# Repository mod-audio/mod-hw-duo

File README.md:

mod-hw-duo
=======================

This repository contains the schematics and PCB design files for the MOD Duo hardware (http://moddevices.com/).

These files were created and can be improved with KiCAD, a free software Electronics CAD which is available at http://www.kicad.org/

This project should work with last revision of KiCad libraries and footprints available at https://github.com/KiCad/

## License

Copyright (c) 2014-2026 MOD Audio Limited.

The hardware design files (schematics, PCB layouts, fabrication files, BOMs) are licensed under
[CC BY-NC-SA 4.0](https://creativecommons.org/licenses/by-nc-sa/4.0/) (see [`LICENSE`](LICENSE)).
You may study, modify, repair and build them for yourself, and share your changes under the same licence.
You may not use them commercially, for example to make or sell boards or devices.

Third-party files (manufacturer component models, symbols and footprints, module documentation) are not covered by
this licence. See [`NOTICE`](NOTICE) for the list.

The MOD logo is a registered trademark (EU trade mark no. 016228827; UK trade mark no. UK00916228827).
The licence gives no right to use the MOD name or logo. See [`NOTICE`](NOTICE).

For commercial licensing, contact MOD Audio.

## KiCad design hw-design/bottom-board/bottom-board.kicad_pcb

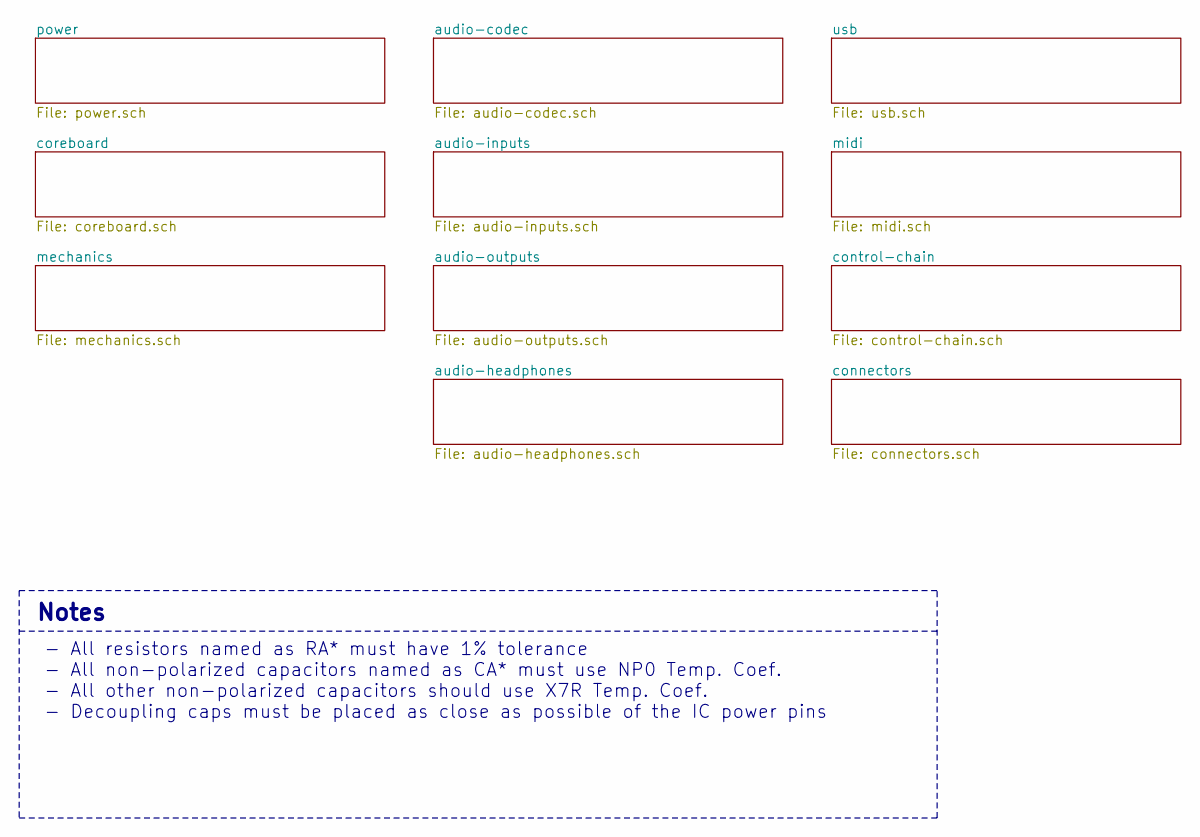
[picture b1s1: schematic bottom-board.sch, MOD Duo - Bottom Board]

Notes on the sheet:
- All resistors named as RA* must have 1% tolerance - All non-polarized capacitors named as CA* must use NP0 Temp. Coef. - All other non-polarized capacitors should use X7R Temp. Coef. - Decoupling caps must be placed as close as possible of the IC power pins
Notes

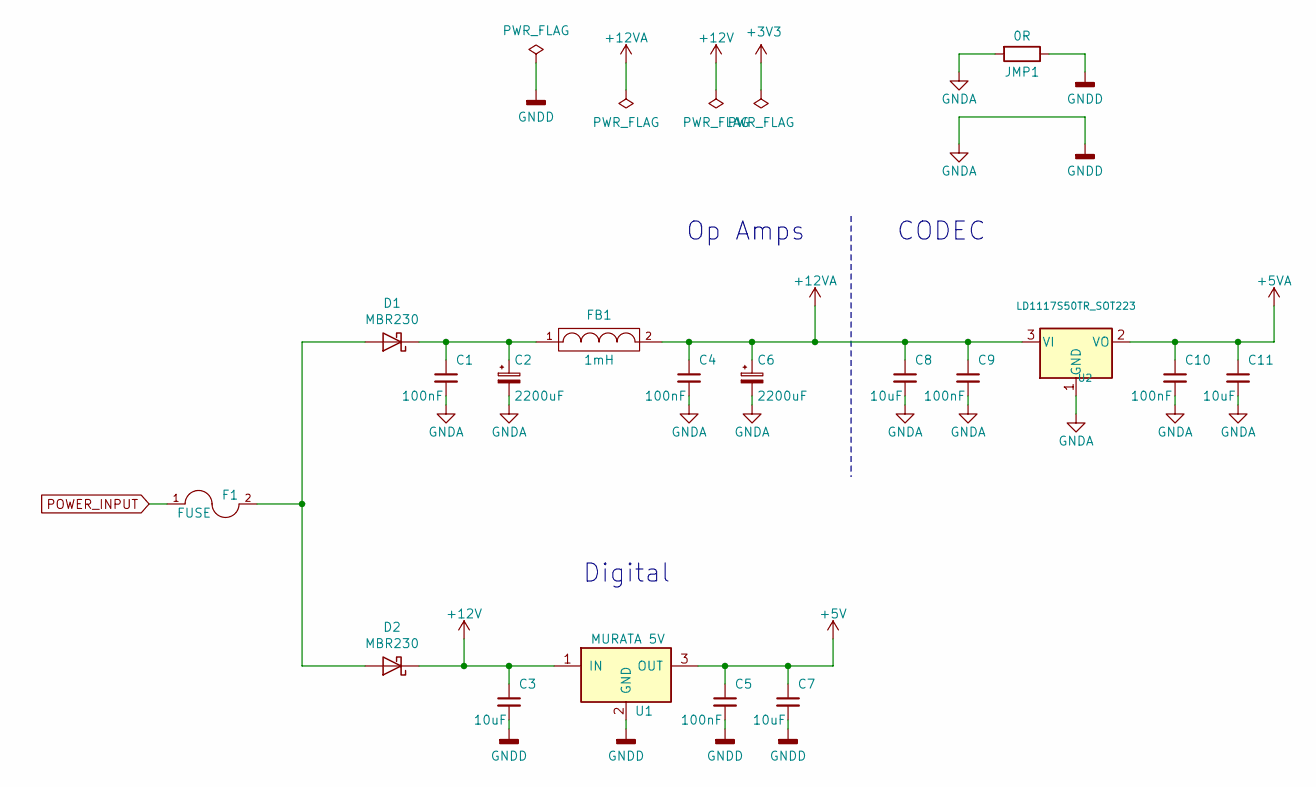
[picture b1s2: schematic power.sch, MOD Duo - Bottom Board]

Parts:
C1, C4, C5, C9, C10: 100nF; C_0603_1608Metric; MPN C1608X7R1E104K080AA
C2, C6: 2200uF; C_Radial_D10_L20_P5; MPN 16PX2200MEFC10X20
C3, C7, C8, C11: 10uF; C_0805_2012Metric; MPN GRM219R61E106KA12D
D1, D2: MBR230; D_SOD-123F
F1: FUSE; Fuse_SMD2920; MPN 0ZCF0200FF2C
FB1: 1mH; SELF-WE-PD-XXL; MPN SRR1260-102K
JMP1: 0R; Jumper_SMD_THT
U1: MURATA 5V; OKI-78SR_Vertical; MPN OKI-78SR-5/1.5-W36-C
U2: LD1117S50TR_SOT223; SOT-223-3_TabPin2; MPN NCP1117DT50G

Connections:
+5V: C5.1, C7.1, U1.3 (OUT); also elsewhere on the board
+5VA: C10.1, C11.1, U2.2 (VO); also elsewhere on the board
+12V: C3.1, D2.1 (K), U1.1 (IN); also elsewhere on the board
+12VA: C4.1, C6.1, C8.1, C9.1, FB1.2, U2.3 (VI); also elsewhere on the board
GNDA: C1.2, C2.2, C3.2, C4.2, C5.2, C6.2, C7.2, C8.2, C9.2, C10.2, C11.2, JMP1.1, JMP1.2, U1.2 (GND), U2.1 (GND); also elsewhere on the board
unnamed: C1.1, C2.1, D1.1 (K), FB1.1
unnamed: D1.2 (A), D2.2 (A), F1.2
POWER_INPUT: F1.1; also elsewhere on the board

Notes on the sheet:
Op Amps
CODEC
Digital

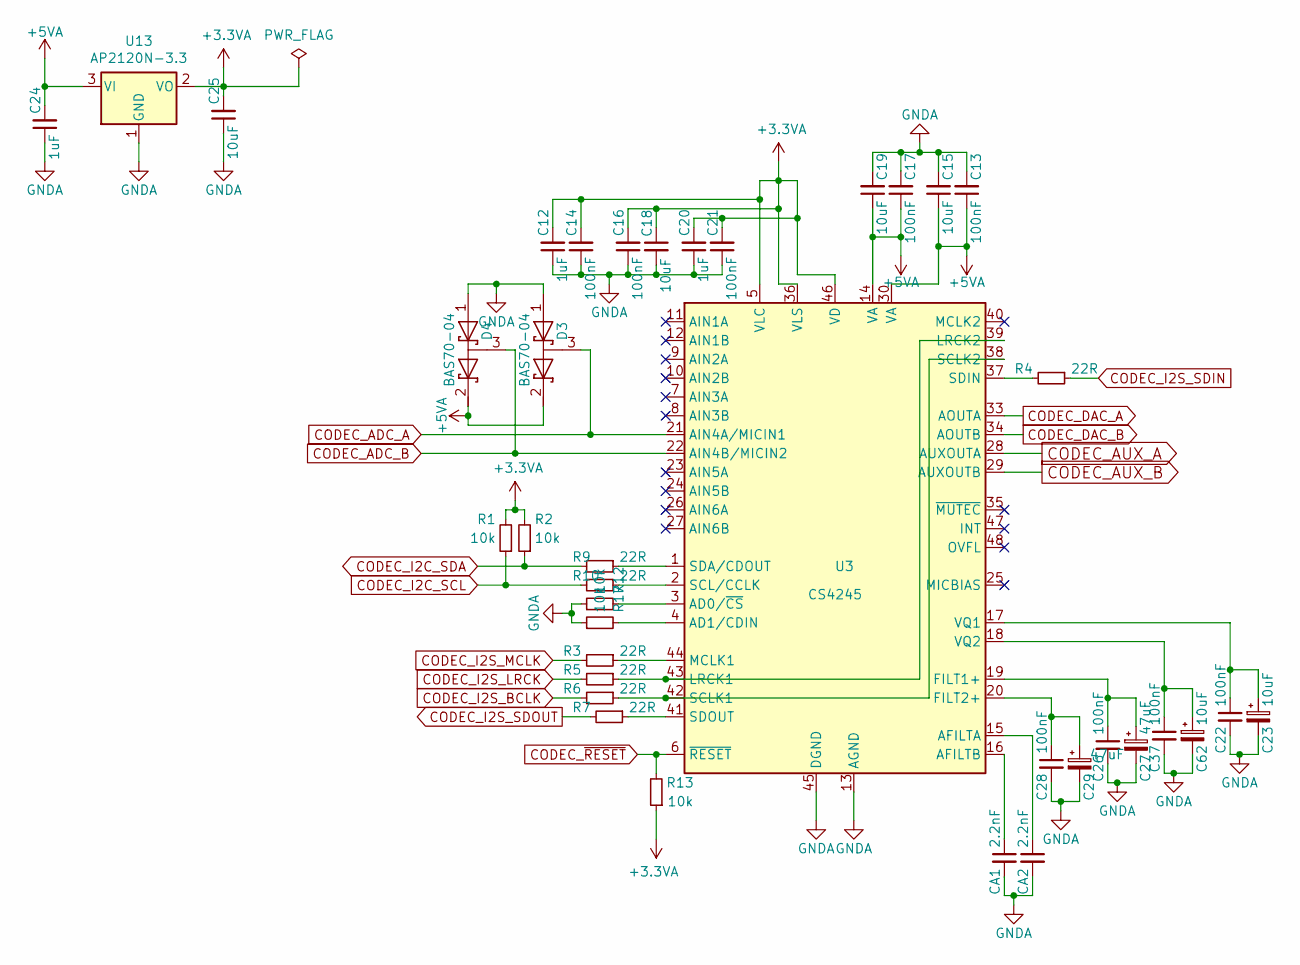
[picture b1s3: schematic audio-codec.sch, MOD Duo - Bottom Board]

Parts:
C12, C20, C24: 1uF; C_0805_2012Metric; MPN C2012X7R1E105K125AB
C13, C14, C16, C17, C21, C22, C26, C28, C37: 100nF; C_0402_1005Metric; MPN C1005X7R1E104K050BB
C15, C18, C19, C25: 10uF; C_0805_2012Metric; MPN GRM219R61E106KA12D
C23, C62: 10uF; CP_Elec_6.3x5.3; MPN UWX1E100MCL1GB
C27, C29: 47uF; CP_Elec_6.3x5.3; MPN UUD1E470MCL1GS
CA1, CA2: 2.2nF; C_0603_1608Metric; MPN GRM1885C1H222JA01D
D3, D4: BAS70-04; SOT-23; MPN BAS70-04-TP
R1, R2, R12, R13, R17: 10k; R_0603_1608Metric; MPN RMCF0603JT10K0
R3, R4, R5, R6, R7, R9, R10: 22R; R_0603_1608Metric; MPN RMCF0603JT22R0
U3: CS4245; LQFP-48_7x7mm_P0.5mm
U13: AP2120N-3.3; SOT-23

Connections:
+3.3VA: C12.2, C14.2, C16.2, C18.1, C20.2, C21.2, C25.2, R1.2, R2.2, R13.1, U3.5 (VLC), U3.36 (VLS), U3.46 (VD), U13.2 (VO)
+5VA: C13.1, C15.1, C17.1, C19.1, C24.2, D3.2 (K), D4.2 (K), U3.14 (VA), U3.30 (VA), U13.3 (VI); also elsewhere on the board
CODEC_ADC_A: D3.3 (common), U3.21 (AIN4A/MICIN1); also elsewhere on the board
CODEC_ADC_B: D4.3 (common), U3.22 (AIN4B/MICIN2); also elsewhere on the board
CODEC_AUX_A: U3.28 (AUXOUTA); also elsewhere on the board
CODEC_AUX_B: U3.29 (AUXOUTB); also elsewhere on the board
CODEC_DAC_A: U3.33 (AOUTA); also elsewhere on the board
CODEC_DAC_B: U3.34 (AOUTB); also elsewhere on the board
CODEC_I2C_SCL: R1.1, R10.2; also elsewhere on the board
CODEC_I2C_SDA: R2.1, R9.2; also elsewhere on the board
CODEC_I2S_BCLK: R6.2; also elsewhere on the board
CODEC_I2S_LRCK: R5.2; also elsewhere on the board
CODEC_I2S_MCLK: R3.2; also elsewhere on the board
CODEC_I2S_SDIN: R4.1; also elsewhere on the board
CODEC_I2S_SDOUT: R7.2; also elsewhere on the board
CODEC_~RESET: R13.2, U3.6 (~RESET); also elsewhere on the board
GNDA: C12.1, C13.2, C14.1, C15.2, C16.1, C17.2, C18.2, C19.2, C20.1, C21.1, C22.2, C23.2, C24.1, C25.1, C26.2, C27.2, C28.2, C29.2, C37.2, C62.2, CA1.2, CA2.2, D3.1 (A), D4.1 (A), R12.1, R17.1, U3.13 (AGND), U3.31 (AGND), U3.32 (AGND), U3.45 (DGND), U13.1 (GND); also elsewhere on the board
unnamed: C22.1, C23.1, U3.17 (VQ1)
unnamed: C26.1, C27.1, U3.19 (FILT1+)
unnamed: C28.1, C29.1, U3.20 (FILT2+)
unnamed: C37.1, C62.1, U3.18 (VQ2)
unnamed: CA1.1, U3.16 (AFILTB)
unnamed: CA2.1, U3.15 (AFILTA)
unnamed: R3.1, U3.44 (MCLK1)
unnamed: R4.2, U3.37 (SDIN)
unnamed: R5.1, U3.39 (LRCK2), U3.43 (LRCK1)
unnamed: R6.1, U3.38 (SCLK2), U3.42 (SCLK1)
unnamed: R7.1, U3.41 (SDOUT)
unnamed: R9.1, U3.1 (SDA/CDOUT)
unnamed: R10.1, U3.2 (SCL/CCLK)
unnamed: R12.2, U3.3 (AD0/~CS)
unnamed: R17.2, U3.4 (AD1/CDIN)

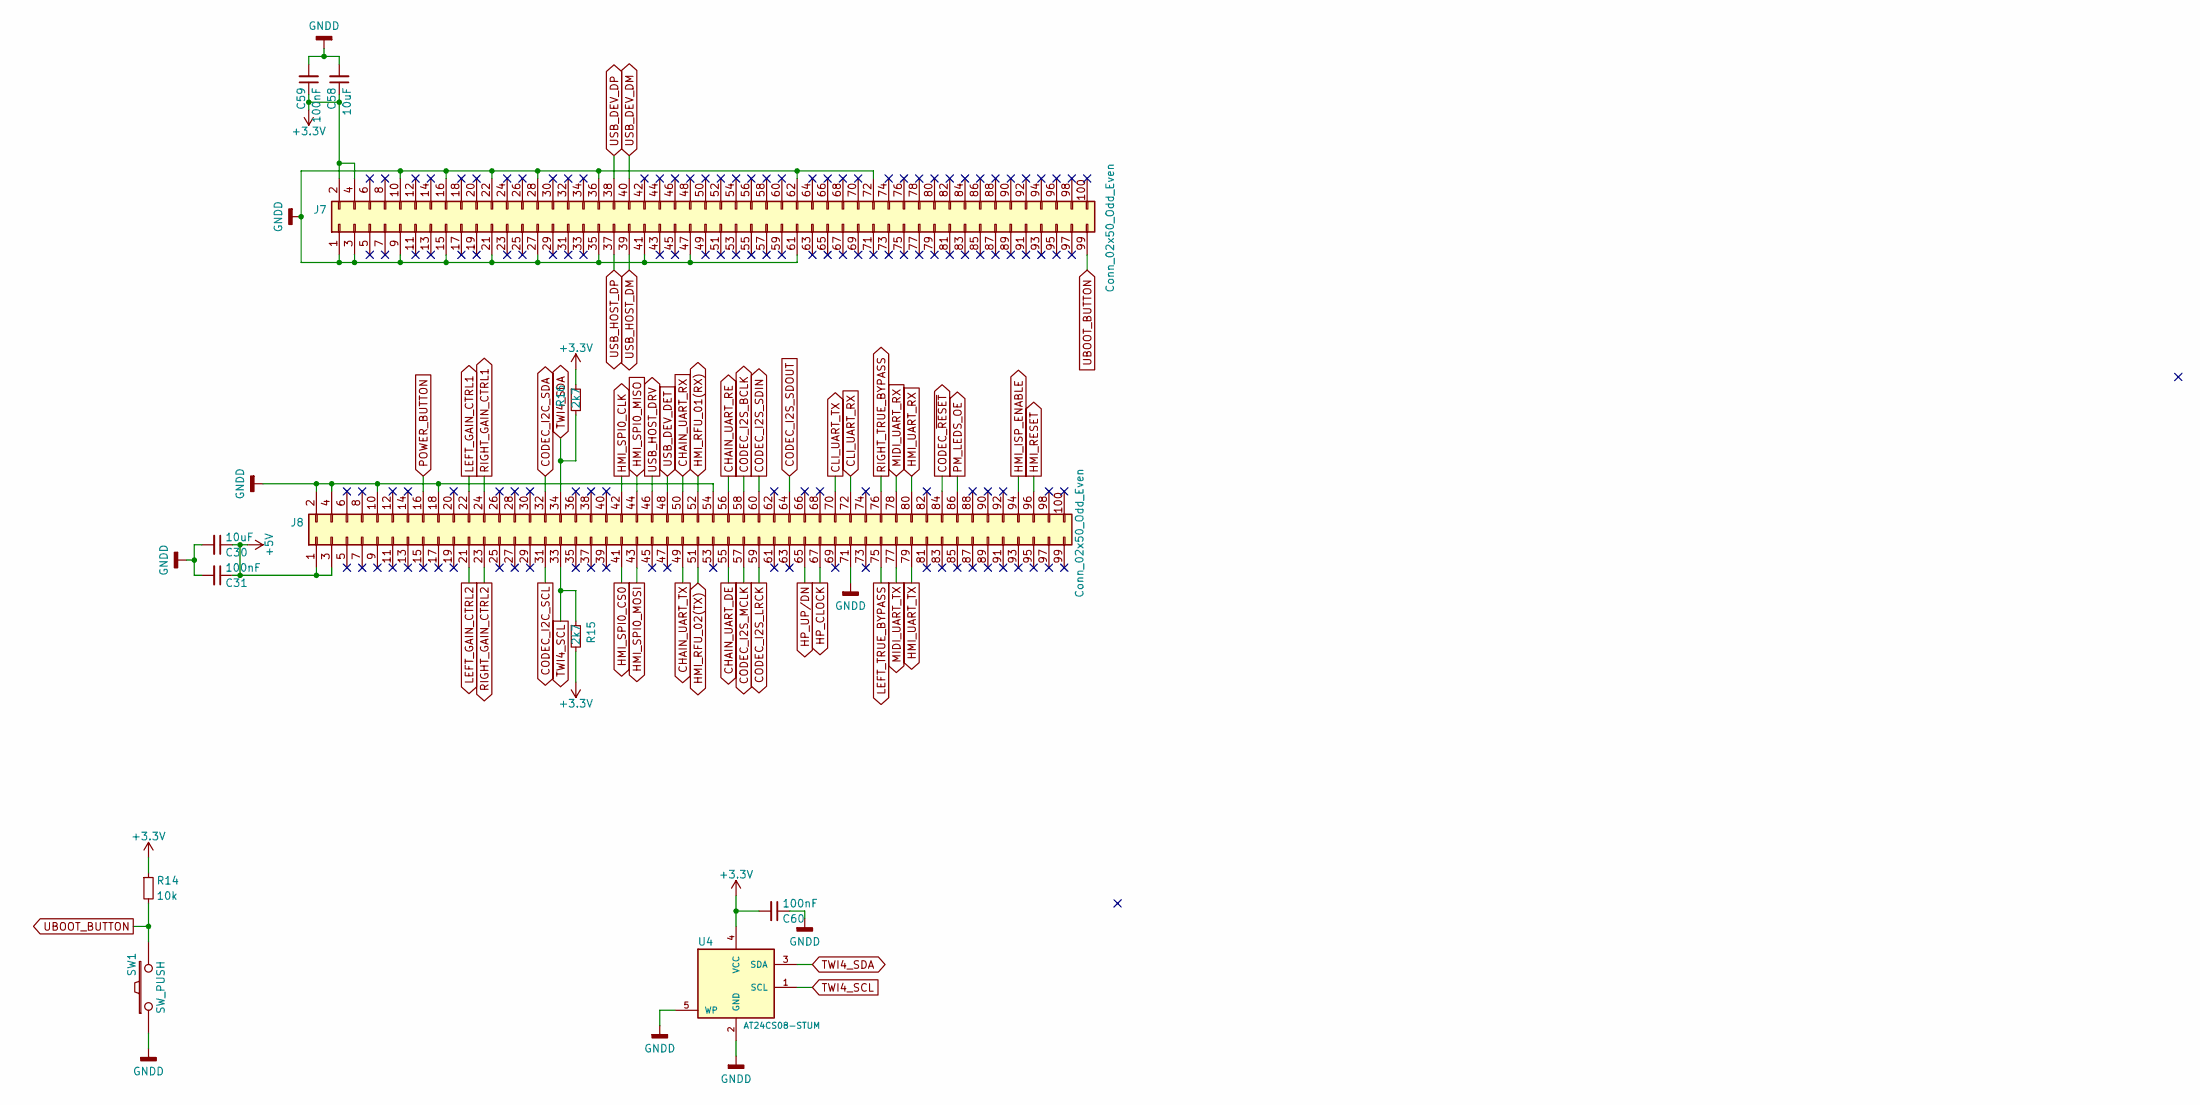
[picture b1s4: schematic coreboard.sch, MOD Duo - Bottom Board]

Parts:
C30, C58: 10uF; C_0805_2012Metric; MPN GRM219R61E106KA12D
C31, C59, C60: 100nF; C_0603_1608Metric; MPN C1608X7R1E104K080AA
J7, J8: Conn_02x50_Odd_Even; Pin_Header_Straight_2x50_Pitch1.27mm_SMD
R14: 10k; R_0603_1608Metric; MPN RMCF0603JT10K0
R15, R16: 2k7; R_0603_1608Metric; MPN RMCF0603JT2K70
SW1: SW_PUSH; SW_Tactile_SPST_Angled; MPN 1825027-2
U4: AT24CS08-STUM; SOT-23-5; MPN AT24CS08-STUM

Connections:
+3V3: C58.1, C59.1, C60.2, J7.2, J7.4, R14.1, R15.2, R16.1, U4.4 (VCC); also elsewhere on the board
+5V: C30.1, C31.1, J8.1, J8.3; also elsewhere on the board
CHAIN_UART_DE: J8.55; also elsewhere on the board
CHAIN_UART_RE: J8.56; also elsewhere on the board
CHAIN_UART_RX: J8.50; also elsewhere on the board
CHAIN_UART_TX: J8.49; also elsewhere on the board
CLI_UART_RX: J8.72; also elsewhere on the board
CLI_UART_TX: J8.70; also elsewhere on the board
CODEC_I2C_SCL: J8.31; also elsewhere on the board
CODEC_I2C_SDA: J8.32; also elsewhere on the board
CODEC_I2S_BCLK: J8.58; also elsewhere on the board
CODEC_I2S_LRCK: J8.59; also elsewhere on the board
CODEC_I2S_MCLK: J8.57; also elsewhere on the board
CODEC_I2S_SDIN: J8.60; also elsewhere on the board
CODEC_I2S_SDOUT: J8.64; also elsewhere on the board
CODEC_~RESET: J8.84; also elsewhere on the board
GNDA: C30.2, C31.2, C58.2, C59.2, C60.1, J7.1, J7.3, J7.9, J7.10, J7.15, J7.16, J7.21, J7.22, J7.27, J7.28, J7.35, J7.36, J7.41, J7.47, J7.61, J7.62, J7.72, J8.2, J8.4, J8.10, J8.18, J8.54, J8.71, SW1.1, U4.2 (GND), U4.5 (WP); also elsewhere on the board
HMI_ISP_ENABLE: J8.94; also elsewhere on the board
HMI_RESET: J8.96; also elsewhere on the board
HMI_RFU_01(RX): J8.52; also elsewhere on the board
HMI_RFU_02(TX): J8.51; also elsewhere on the board
HMI_SPI0_CLK: J8.42; also elsewhere on the board
HMI_SPI0_CS0: J8.41; also elsewhere on the board
HMI_SPI0_MISO: J8.44; also elsewhere on the board
HMI_SPI0_MOSI: J8.43; also elsewhere on the board
HMI_UART_RX: J8.80; also elsewhere on the board
HMI_UART_TX: J8.79; also elsewhere on the board
HP_CLOCK: J8.67; also elsewhere on the board
HP_UP/DN: J8.65; also elsewhere on the board
LEFT_GAIN_CTRL1: J8.22; also elsewhere on the board
LEFT_GAIN_CTRL2: J8.21; also elsewhere on the board
LEFT_TRUE_BYPASS: J8.75; also elsewhere on the board
MIDI_UART_RX: J8.78; also elsewhere on the board
MIDI_UART_TX: J8.77; also elsewhere on the board
PM_LEDS_OE: J8.86; also elsewhere on the board
POWER_BUTTON: J8.16; also elsewhere on the board
RIGHT_GAIN_CTRL1: J8.24; also elsewhere on the board
RIGHT_GAIN_CTRL2: J8.23; also elsewhere on the board
RIGHT_TRUE_BYPASS: J8.76; also elsewhere on the board
TWI4_SCL: J8.33, R15.1, U4.1 (SCL); also elsewhere on the board
TWI4_SDA: J8.34, R16.2, U4.3 (SDA); also elsewhere on the board
UBOOT_BUTTON: J7.99, R14.2, SW1.2
USB_DEV_DET: J8.48; also elsewhere on the board
USB_DEV_DM: J7.40; also elsewhere on the board
USB_DEV_DP: J7.38; also elsewhere on the board
USB_HOST_DM: J7.39; also elsewhere on the board
USB_HOST_DP: J7.37; also elsewhere on the board
USB_HOST_DRV: J8.46; also elsewhere on the board

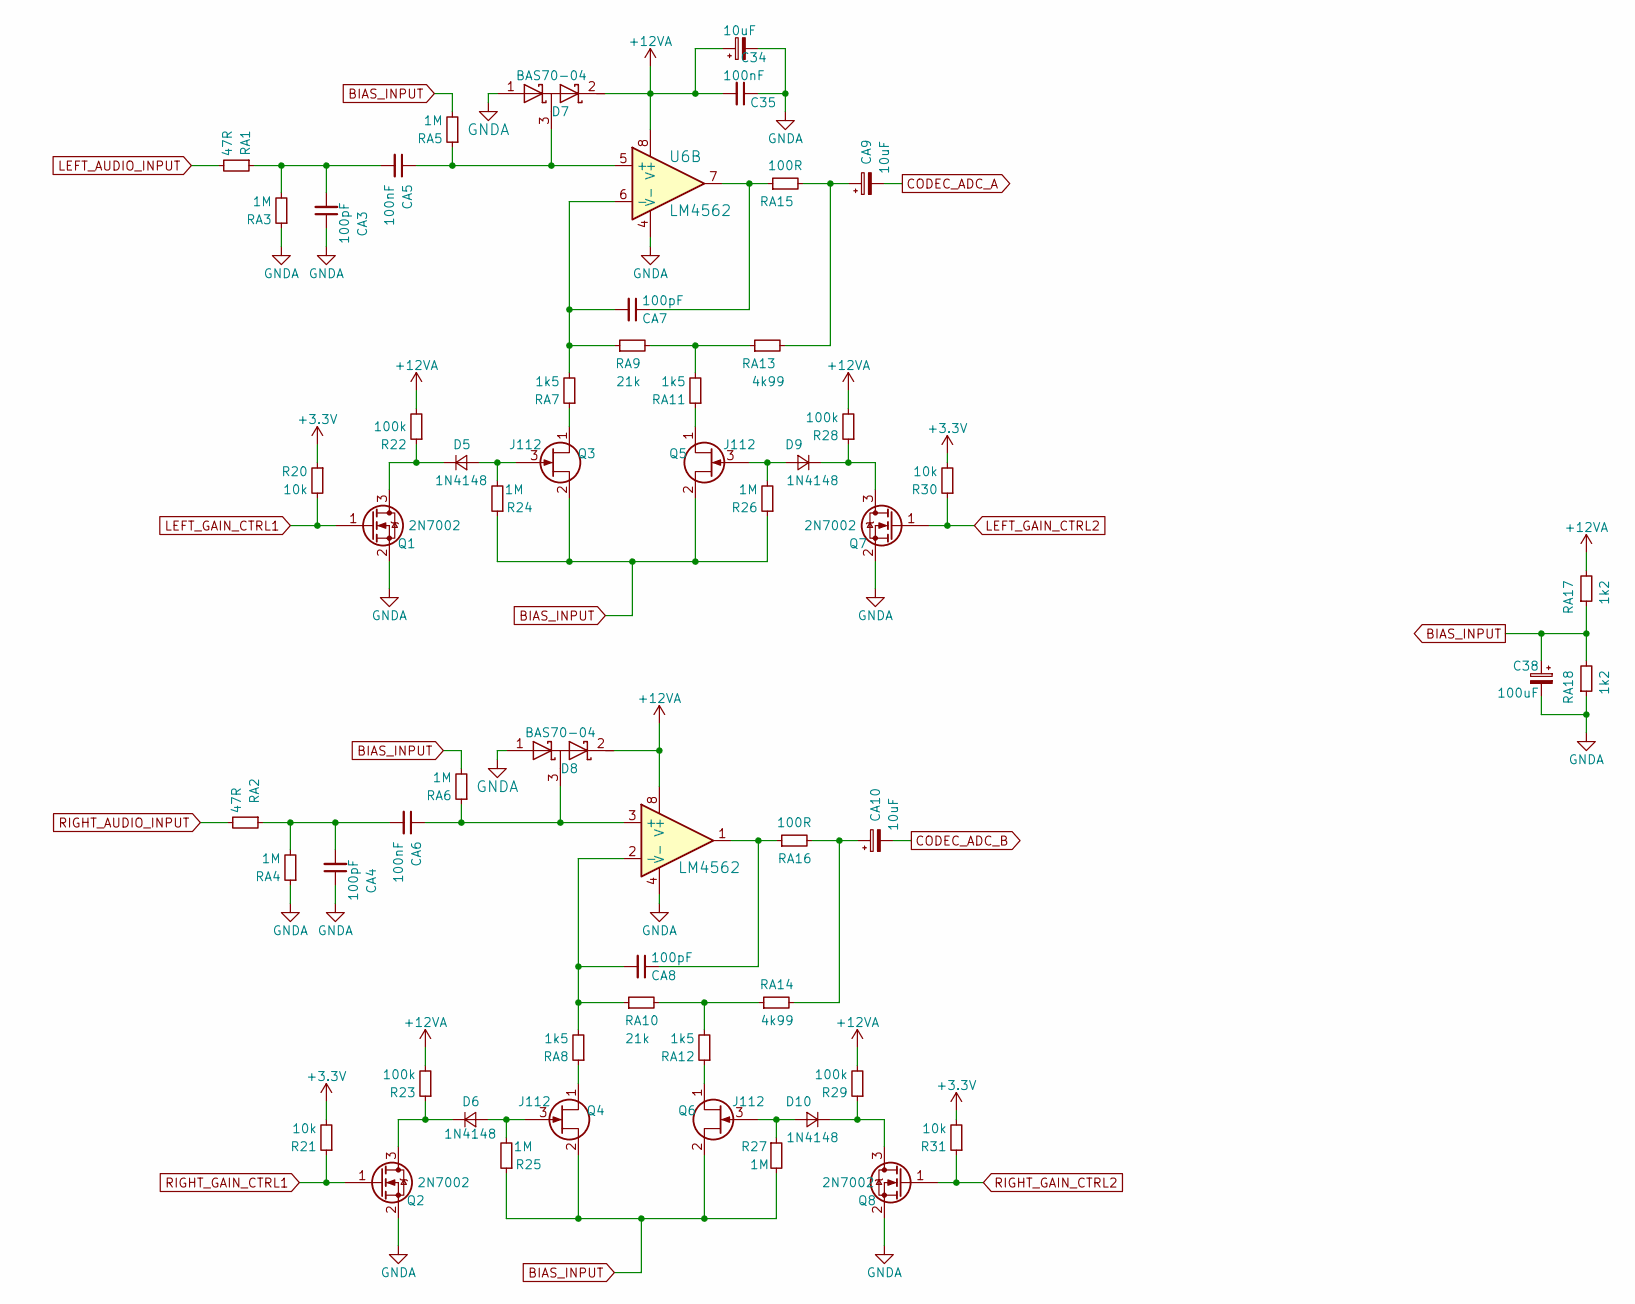
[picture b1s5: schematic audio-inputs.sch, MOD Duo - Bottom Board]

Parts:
C34: 10uF; CP_Elec_5x5.3; MPN UWX1E100MCL1GB
C35: 100nF; C_0603_1608Metric; MPN C1608X7R1E104K080AA
C38: 100uF; CP_Elec_6.3x5.3; MPN UWX1C101MCL1GB
CA3, CA4, CA7, CA8: 100pF; C_0603_1608Metric; MPN C1608C0G1H101J080AA
CA5, CA6: 100nF; C_1206_3216Metric; MPN C1206C104J3GACTU
CA9, CA10: 10uF; CP_Elec_5x5.3; MPN UWX1E100MCL1GB
D5, D6, D9, D10: 1N4148; D_SOD-323; MPN 1N4148WX-TP
D7, D8: BAS70-04; SOT-23; MPN BAS70-04-TP
Q1, Q2, Q7, Q8: 2N7002; SOT-23; MPN 2N7002P,215
Q3, Q4, Q5, Q6: J112; SOT-23; MPN MMBFJ112
R20, R21, R30, R31: 10k; R_0603_1608Metric; MPN RMCF0603JT10K0
R22, R23, R28, R29: 100k; R_0603_1608Metric; MPN RMCF0603JT100K
R24, R25, R26, R27: 1M; R_0603_1608Metric; MPN RMCF0603JT1M00
RA1, RA2: 47R; R_0603_1608Metric; MPN ERA-3AEB470V
RA3, RA4, RA5, RA6: 1M; R_0603_1608Metric; MPN CPF0603B1M0E
RA7, RA8, RA11, RA12: 1k5; R_0603_1608Metric; MPN ERA-3AEB152V
RA9, RA10: 21k; R_0603_1608Metric; MPN ERA-3AEB2102V
RA13, RA14: 4k99; R_0603_1608Metric; MPN ERA-3AEB4991V
RA15, RA16: 100R; R_0603_1608Metric; MPN ERA-3AEB101V
RA17, RA18: 1k2; R_0603_1608Metric; MPN ERA-3AEB122V
U6: LM4562; SOIC-8_3.9x4.9mm_P1.27mm; MPN LM4562MAX/NOPB

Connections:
+3V3: R20.1, R21.2, R30.2, R31.2; also elsewhere on the board
+12VA: C34.1, C35.2, D7.2 (K), D8.2 (K), R22.2, R23.2, R28.2, R29.2, RA17.2, U6.8 (V+); also elsewhere on the board
BIAS_INPUT: C38.1, Q3.2 (S), Q4.2 (S), Q5.2 (S), Q6.2 (S), R24.1, R25.1, R26.1, R27.2, RA5.2, RA6.2, RA17.1, RA18.2
CODEC_ADC_A: CA9.2; also elsewhere on the board
CODEC_ADC_B: CA10.2; also elsewhere on the board
GNDA: C34.2, C35.1, C38.2, CA3.1, CA4.1, D7.1 (A), D8.1 (A), Q1.2 (S), Q2.2 (S), Q7.2 (S), Q8.2 (S), RA3.1, RA4.1, RA18.1, U6.4 (V-); also elsewhere on the board
LEFT_AUDIO_INPUT: RA1.2; also elsewhere on the board
LEFT_GAIN_CTRL1: Q1.1 (G), R20.2; also elsewhere on the board
LEFT_GAIN_CTRL2: Q7.1 (G), R30.1; also elsewhere on the board
unnamed: CA3.2, CA5.2, RA1.1, RA3.2
unnamed: CA4.2, CA6.2, RA2.1, RA4.2
unnamed: CA5.1, D7.3 (common), RA5.1, U6.5 (+)
unnamed: CA6.1, D8.3 (common), RA6.1, U6.3 (+)
unnamed: CA7.1, RA15.1, U6.7
unnamed: CA7.2, RA7.2, RA9.1, U6.6 (-)
unnamed: CA8.1, RA16.1, U6.1
unnamed: CA8.2, RA8.2, RA10.1, U6.2 (-)
unnamed: CA9.1, RA13.2, RA15.2
unnamed: CA10.1, RA14.2, RA16.2
unnamed: D5.1 (K), Q1.3 (D), R22.1
unnamed: D5.2 (A), Q3.3 (G), R24.2
unnamed: D6.1 (K), Q2.3 (D), R23.1
unnamed: D6.2 (A), Q4.3 (G), R25.2
unnamed: D9.1 (K), Q7.3 (D), R28.1
unnamed: D9.2 (A), Q5.3 (G), R26.2
unnamed: D10.1 (K), Q8.3 (D), R29.1
unnamed: D10.2 (A), Q6.3 (G), R27.1
unnamed: Q3.1 (D), RA7.1
unnamed: Q4.1 (D), RA8.1
unnamed: Q5.1 (D), RA11.1
unnamed: Q6.1 (D), RA12.1
unnamed: RA10.2, RA12.2, RA14.1
unnamed: RA9.2, RA11.2, RA13.1
RIGHT_AUDIO_INPUT: RA2.2; also elsewhere on the board
RIGHT_GAIN_CTRL1: Q2.1 (G), R21.1; also elsewhere on the board
RIGHT_GAIN_CTRL2: Q8.1 (G), R31.1; also elsewhere on the board

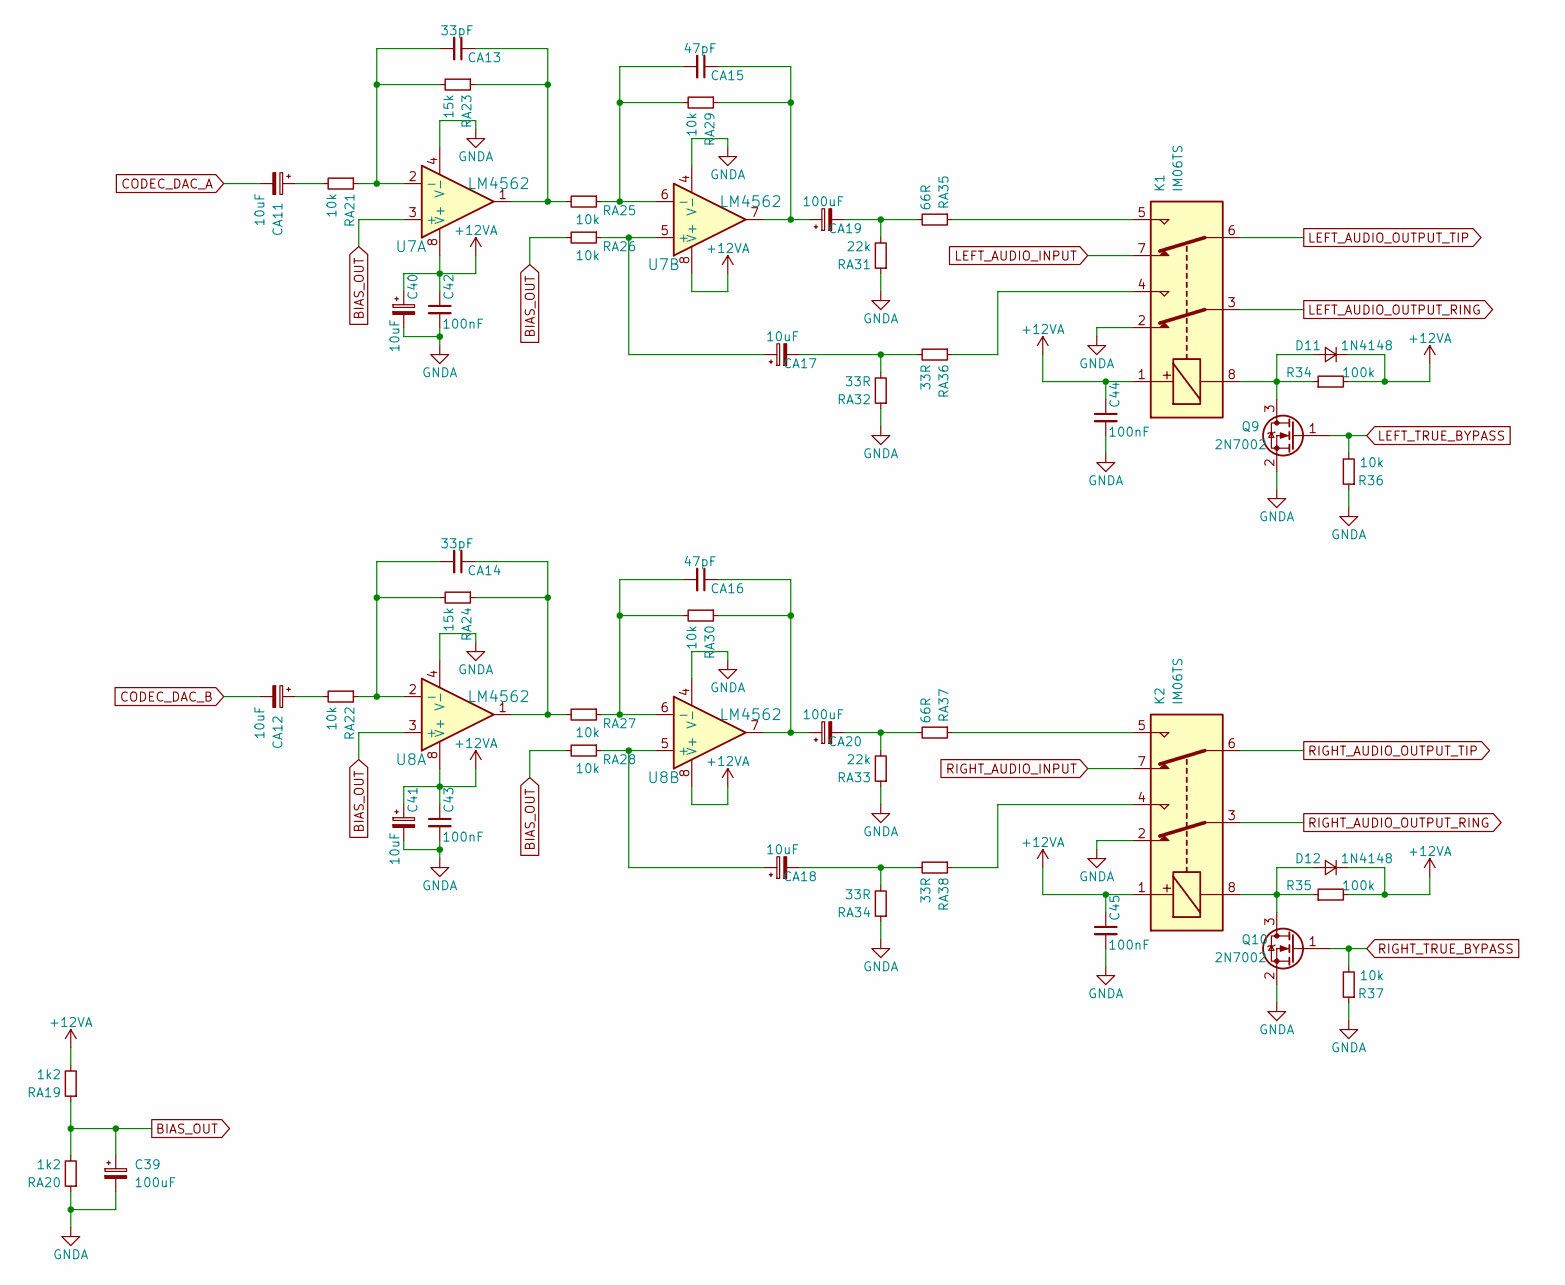
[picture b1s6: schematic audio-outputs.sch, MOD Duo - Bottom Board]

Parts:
C39: 100uF; CP_Elec_6.3x5.3; MPN UWX1C101MCL1GB
C40, C41: 10uF; CP_Elec_5x5.3; MPN UWX1E100MCL1GB
C42, C43, C44, C45: 100nF; C_0603_1608Metric; MPN C1608X7R1E104K080AA
CA11, CA12, CA17, CA18: 10uF; CP_Elec_5x5.3; MPN UWX1E100MCL1GB
CA13, CA14: 33pF; C_0603_1608Metric; MPN C1608C0G1H330J080AA
CA15, CA16: 47pF; C_0603_1608Metric; MPN C1608C0G1H470J080AA
CA19, CA20: 100uF; CP_Elec_6.3x7.7; MPN UWT1E101MCL1GS
D11, D12: 1N4148; D_SOD-323; MPN 1N4148WX-TP
K1, K2: IM06TS; Relay_DPDT_Omron_G6S-2F-good_pinout; MPN IM06TS
Q9, Q10: 2N7002; SOT-23; MPN 2N7002P,215
R34, R35: 100k; R_0603_1608Metric; MPN RMCF0603JT100K
R36, R37: 10k; R_0603_1608Metric; MPN RMCF0603JT10K0
RA19, RA20: 1k2; R_0603_1608Metric; MPN ERA-3AEB122V
RA21, RA22, RA25, RA26, RA27, RA28, RA29, RA30: 10k; R_0603_1608Metric; MPN ERA-3AEB103V
RA23, RA24: 15k; R_0603_1608Metric; MPN ERA-3AEB153V
RA31, RA33: 22k; R_0603_1608Metric; MPN ERA-3AEB223V
RA32, RA34, RA36, RA38: 33R; R_0603_1608Metric; MPN CPF0603B33RE
RA35, RA37: 66R; R_0603_1608Metric; MPN ERA-3AEB66R5V
U7, U8: LM4562; SOIC-8_3.9x4.9mm_P1.27mm; MPN LM4562MAX/NOPB

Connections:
+12VA: C40.1, C41.1, C42.1, C43.1, C44.1, C45.1, D11.1 (K), D12.1 (K), K1.1, K2.1, R34.2, R35.2, RA19.2, U7.8 (V+), U8.8 (V+); also elsewhere on the board
BIAS_OUT: C39.1, RA19.1, RA20.2, RA26.2, RA28.2, U7.3 (+), U8.3 (+)
CODEC_DAC_A: CA11.2; also elsewhere on the board
CODEC_DAC_B: CA12.2; also elsewhere on the board
GNDA: C39.2, C40.2, C41.2, C42.2, C43.2, C44.2, C45.2, K1.2, K2.2, Q9.2 (S), Q10.2 (S), R36.1, R37.1, RA20.1, RA31.1, RA32.1, RA33.1, RA34.1, U7.4 (V-), U8.4 (V-); also elsewhere on the board
LEFT_AUDIO_INPUT: K1.7; also elsewhere on the board
LEFT_AUDIO_OUTPUT_RING: K1.3; also elsewhere on the board
LEFT_AUDIO_OUTPUT_TIP: K1.6; also elsewhere on the board
LEFT_TRUE_BYPASS: Q9.1 (G), R36.2; also elsewhere on the board
unnamed: CA11.1, RA21.2
unnamed: CA12.1, RA22.2
unnamed: CA13.1, RA23.1, RA25.2, U7.1
unnamed: CA13.2, RA21.1, RA23.2, U7.2 (-)
unnamed: CA14.1, RA24.1, RA27.2, U8.1
unnamed: CA14.2, RA22.1, RA24.2, U8.2 (-)
unnamed: CA15.1, CA19.1, RA29.1, U7.7
unnamed: CA15.2, RA25.1, RA29.2, U7.6 (-)
unnamed: CA16.1, CA20.1, RA30.1, U8.7
unnamed: CA16.2, RA27.1, RA30.2, U8.6 (-)
unnamed: CA17.1, RA26.1, U7.5 (+)
unnamed: CA17.2, RA32.2, RA36.2
unnamed: CA18.1, RA28.1, U8.5 (+)
unnamed: CA18.2, RA34.2, RA38.2
unnamed: CA19.2, RA31.2, RA35.2
unnamed: CA20.2, RA33.2, RA37.2
unnamed: D11.2 (A), K1.8, Q9.3 (D), R34.1
unnamed: D12.2 (A), K2.8, Q10.3 (D), R35.1
unnamed: K1.4, RA36.1
unnamed: K1.5, RA35.1
unnamed: K2.4, RA38.1
unnamed: K2.5, RA37.1
RIGHT_AUDIO_INPUT: K2.7; also elsewhere on the board
RIGHT_AUDIO_OUTPUT_RING: K2.3; also elsewhere on the board
RIGHT_AUDIO_OUTPUT_TIP: K2.6; also elsewhere on the board
RIGHT_TRUE_BYPASS: Q10.1 (G), R37.2; also elsewhere on the board

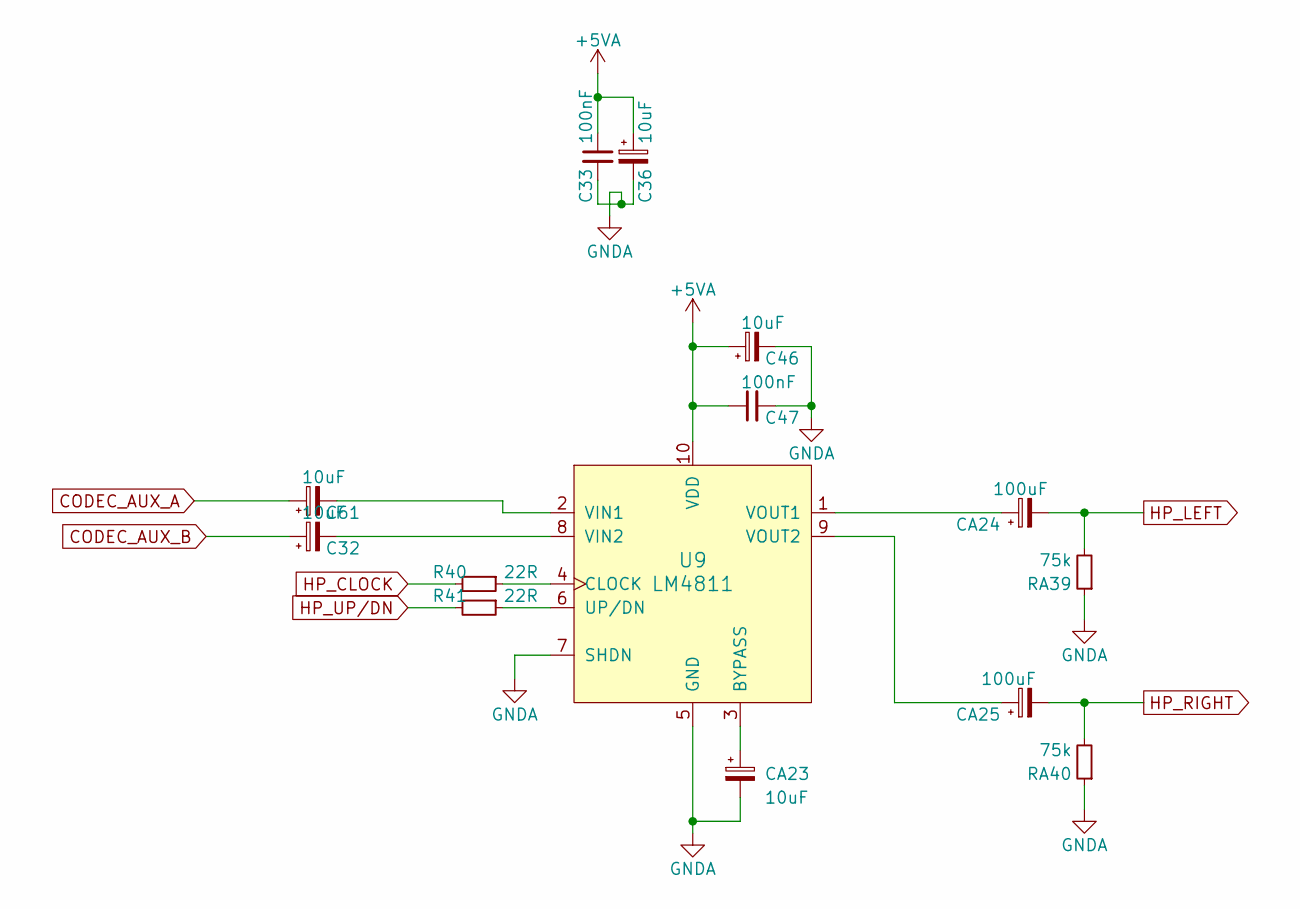
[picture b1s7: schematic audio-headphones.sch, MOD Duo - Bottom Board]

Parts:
C32, C36, C46, C61: 10uF; CP_Elec_5x5.3; MPN UWX1E100MCL1GB
C33, C47: 100nF; C_0603_1608Metric; MPN C1608X7R1E104K080AA
CA23: 10uF; CP_Elec_5x5.3; MPN UWX1E100MCL1GB
CA24, CA25: 100uF; CP_Elec_6.3x7.7; MPN UWT1E101MCL1GS
R40, R41: 22R; R_0603_1608Metric; MPN RMCF0603JT22R0
RA39, RA40: 75k; R_0603_1608Metric; MPN ERA-3AEB753V
U9: LM4811; MSOP-10_3x3mm_Pitch0.5mm; MPN LM4811MM/NOPB

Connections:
+5VA: C33.1, C36.1, C46.1, C47.1, U9.10 (VDD); also elsewhere on the board
CODEC_AUX_A: C61.1; also elsewhere on the board
CODEC_AUX_B: C32.1; also elsewhere on the board
GNDA: C33.2, C36.2, C46.2, C47.2, CA23.2, RA39.1, RA40.1, U9.5 (GND), U9.7 (SHDN); also elsewhere on the board
HP_CLOCK: R40.2; also elsewhere on the board
HP_LEFT: CA24.2, RA39.2; also elsewhere on the board
HP_RIGHT: CA25.2, RA40.2; also elsewhere on the board
HP_UP/DN: R41.2; also elsewhere on the board
unnamed: C32.2, U9.8 (VIN2)
unnamed: C61.2, U9.2 (VIN1)
unnamed: CA23.1, U9.3 (BYPASS)
unnamed: CA24.1, U9.1 (VOUT1)
unnamed: CA25.1, U9.9 (VOUT2)
unnamed: R40.1, U9.4 (CLOCK)
unnamed: R41.1, U9.6 (UP/DN)

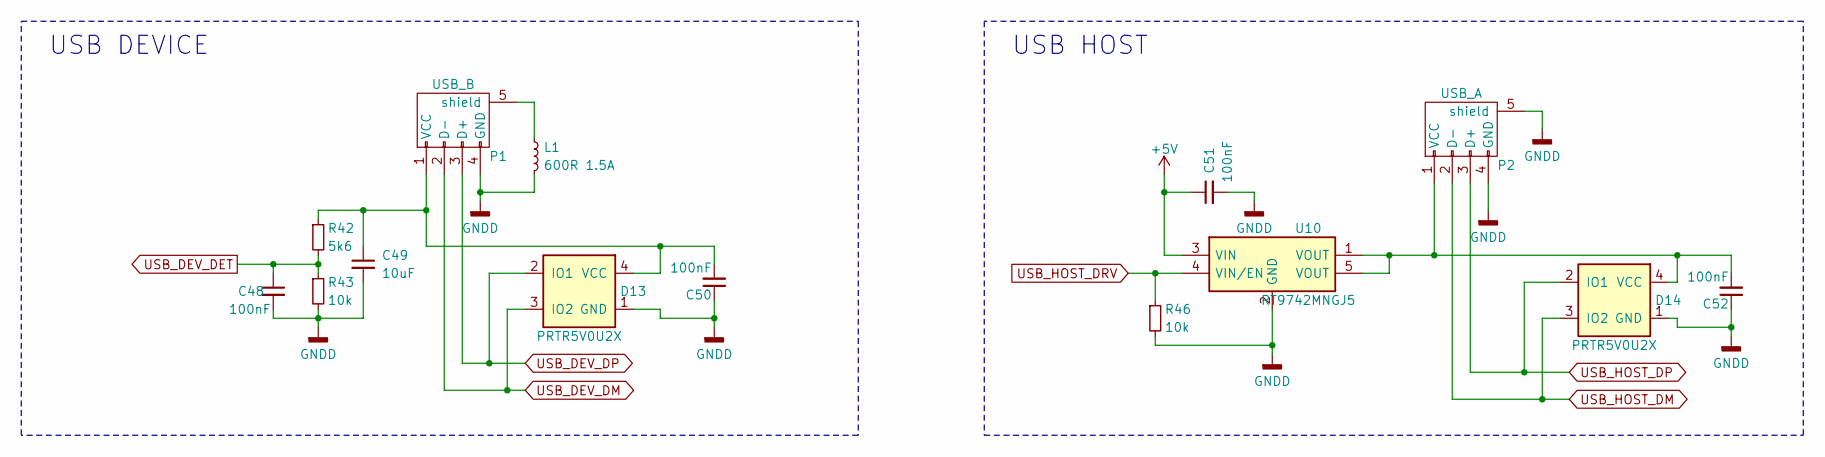
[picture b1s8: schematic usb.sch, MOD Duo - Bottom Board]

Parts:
C48, C50, C51, C52: 100nF; C_0603_1608Metric; MPN C1608X7R1E104K080AA
C49: 10uF; C_0805_2012Metric; MPN GRM219R61E106KA12D
D13, D14: PRTR5V0U2X; SOT-143; MPN PRTR5V0U2X,215
L1: 600R 1.5A; C_0805_2012Metric; MPN MI0805K601R-10
P1: USB_B; USB_B_OST_USB-B1HSxx_Horizontal; MPN 61729-1011BLF
P2: USB_A; USB_A_Vertical; MPN 73725-0110BLF
R42: 5k6; R_0603_1608Metric; MPN RMCF0603JT5K60
R43, R46: 10k; R_0603_1608Metric; MPN RMCF0603JT10K0
U10: RT9742MNGJ5; SOT-23-5; MPN RT9742MNGJ5

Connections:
+5V: C51.1, U10.3 (VIN); also elsewhere on the board
GNDA: C48.2, C49.2, C50.1, C51.2, C52.1, D13.1 (GND), D14.1 (GND), L1.2, P1.4 (GND), P2.4 (GND), P2.5 (shield), R43.2, R46.2, U10.2 (GND); also elsewhere on the board
unnamed: C49.1, C50.2, D13.4 (VCC), P1.1 (VCC), R42.1
unnamed: C52.2, D14.4 (VCC), P2.1 (VCC), U10.1 (VOUT), U10.5 (VOUT)
unnamed: L1.1, P1.5 (shield)
USB_DEV_DET: C48.1, R42.2, R43.1; also elsewhere on the board
USB_DEV_DM: D13.3 (IO2), P1.2 (D-); also elsewhere on the board
USB_DEV_DP: D13.2 (IO1), P1.3 (D+); also elsewhere on the board
USB_HOST_DM: D14.3 (IO2), P2.2 (D-); also elsewhere on the board
USB_HOST_DP: D14.2 (IO1), P2.3 (D+); also elsewhere on the board
USB_HOST_DRV: R46.1, U10.4 (VIN/EN); also elsewhere on the board

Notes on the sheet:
USB DEVICE
USB HOST

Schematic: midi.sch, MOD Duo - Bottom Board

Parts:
C53: 100nF; C_0603_1608Metric; MPN C1608X7R1E104K080AA
D15, D16: 1N4148; SOD-323; MPN 1N4148WX-TP
P3, P4: DIN_5; SDS-50J; MPN SDS-50J
Q12, Q13: 2N7002; SOT-23; MPN 2N7002P,215
R47, R49, R50: 220R; R_0805_2012Metric; MPN ERJ-P06J221V
R48, R51, R52: 10k; R_0603_1608Metric; MPN RMCF0603JT10K0
U11: 6N137S; DIP-8_SMD; MPN 6N137S

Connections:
+3V3: R48.2; also elsewhere on the board
+5V: C53.1, R49.2, R51.1, R52.1, U11.8; also elsewhere on the board
GNDA: C53.2, P4.2, Q12.2 (S), Q13.2 (S), U11.5; also elsewhere on the board
MIDI_UART_RX: D16.2 (A), R48.1; also elsewhere on the board
MIDI_UART_TX: Q13.1 (G); also elsewhere on the board
unnamed: D15.1 (K), R47.1, U11.2
unnamed: D15.2 (A), P3.5, U11.3
unnamed: D16.1 (K), U11.6
unnamed: P3.4, R47.2
unnamed: P4.4, R49.1
unnamed: P4.5, R50.1
unnamed: Q12.1 (G), Q13.3 (D), R52.2
unnamed: Q12.3 (D), R50.2, R51.2

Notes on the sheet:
MIDI IN
MIDI OUT

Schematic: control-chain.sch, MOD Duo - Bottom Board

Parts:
C54: 100nF; C_0603_1608Metric; MPN C1608X7R1E104K080AA
Q14, Q15: BSS84; SOT-23; MPN BSS84
R53, R54, R57, R58: 10k; R_0603_1608Metric; MPN RMCF0603JT10K0
R55, R56: 100R; R_0603_1608Metric; MPN RMCF0603JT100R
R59, R60, R61, R62: 56R; R_0805_2012Metric; MPN ERJ-P6WJ560V
R63: 100R; R_0805_2012Metric; MPN ERJ-P06J101V
U12: ISL83491; SOIC-14_3.9x8.7mm_P1.27mm; MPN ISL83491IBZ

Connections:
+3V3: C54.1, Q14.2 (S), Q15.2 (S), R57.1, U12.13 (VCC), U12.14 (VCC); also elsewhere on the board
CHAIN_UART_DE: R58.1, U12.4 (DE); also elsewhere on the board
CHAIN_UART_RE: R57.2, U12.3 (~RE); also elsewhere on the board
CHAIN_UART_RX: Q15.1 (G), R56.2; also elsewhere on the board
CHAIN_UART_TX: R55.2; also elsewhere on the board
GNDA: C54.2, R53.2, R54.2, R58.2, U12.6 (GND), U12.7 (GND); also elsewhere on the board
unnamed: Q14.1 (G), R55.1, U12.5 (DI)
unnamed: R56.1, U12.2 (RO)
unnamed: R59.2, U12.12 (A)
unnamed: R60.2, U12.11 (~B)
unnamed: R61.2, U12.9 (Y)
unnamed: R62.2, U12.10 (~Z~)
RS485_RX+: R59.1, R63.1; also elsewhere on the board
RS485_RX-: R60.1, R63.2; also elsewhere on the board
RS485_RX_LED: Q15.3 (D), R54.1; also elsewhere on the board
RS485_TX+: R61.1; also elsewhere on the board
RS485_TX-: R62.1; also elsewhere on the board
RS485_TX_LED: Q14.3 (D), R53.1; also elsewhere on the board
